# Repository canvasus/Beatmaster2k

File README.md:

# Beatmaster2k

A rudimentary step sequencer based on a Teensy 4.1 and a Novation Launchpad. 
It is mainly intended as a "jamming partner", not a full-fledged production tool.

Some basic features/specs:

- 7 Tracks. Can be set to output midi on serial, device or host ports
- 8 Patterns per track currently, but lots of room for expansion
- 64 Scenes, i.e combination of patterns

- Patterns are edited on the Launchpad. Works during playing
- Patterns can be set to any length between 1 and 128 steps
- Patterns have configurable speed

- Patterns and other settings stored on SD card

Component list:
- Teensy 4.1
- SD card
- ILI9341 display (touch is not used atm)
- 2 encoders
- 8 buttons via an MPC23017 expander
- Powered usb hub
- Novation Launchpad Mini Mk3

(prototype assembly)

(parts for 3D print and milling in Onshape)

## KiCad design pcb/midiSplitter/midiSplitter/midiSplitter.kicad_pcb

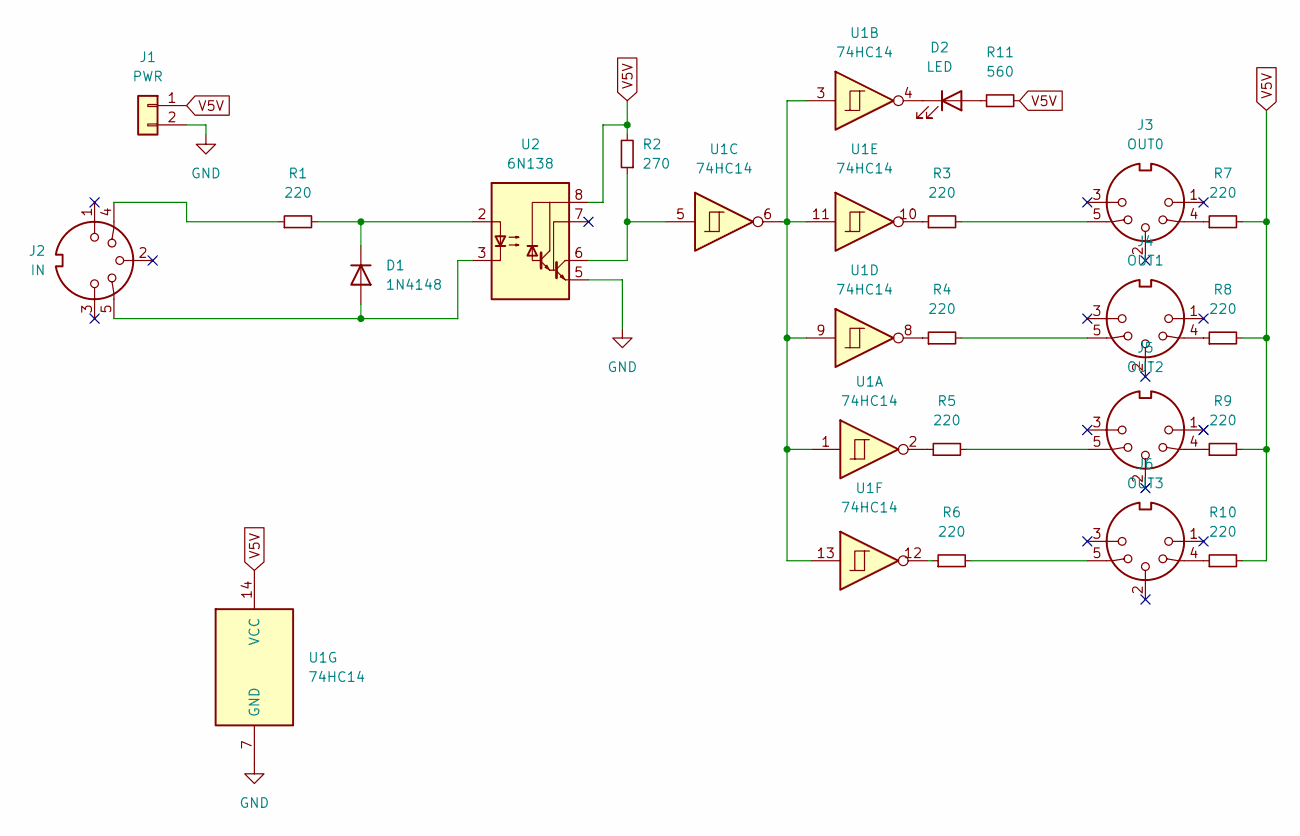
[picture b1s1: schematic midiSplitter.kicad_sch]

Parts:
D1: 1N4148; D_DO-35_SOD27_P7.62mm_Horizontal
D2: LED; LED_D3.0mm
J1: PWR; PinHeader_1x02_P2.54mm_Vertical
J2: IN; MIDI_DIN5
J3: OUT0; MIDI_DIN5
J4: OUT1; MIDI_DIN5
J5: OUT2; MIDI_DIN5
J6: OUT3; MIDI_DIN5
R1, R3, R4, R5, R6, R7, R8, R9, R10: 220; R_Axial_DIN0204_L3.6mm_D1.6mm_P5.08mm_Horizontal
R2: 270; R_Axial_DIN0204_L3.6mm_D1.6mm_P5.08mm_Horizontal
R11: 560; R_Axial_DIN0204_L3.6mm_D1.6mm_P5.08mm_Horizontal
U1: 74HC14; DIP-14_W7.62mm
U2: 6N138; DIP-8_W7.62mm

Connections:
GND: J1.2, U1.7 (GND), U2.5 (GND)
unnamed: D1.1 (K), R1.2, U2.2 (C1)
unnamed: D1.2 (A), J2.5, U2.3 (C2)
unnamed: D2.2 (A), R11.1
unnamed: J2.4, R1.1
unnamed: R2.1, U1.5, U2.6 (VO2)
unnamed: R3.1, U1.10
unnamed: J3.5, R3.2
unnamed: R4.1, U1.8
unnamed: J4.5, R4.2
unnamed: R5.1, U1.2
unnamed: J5.5, R5.2
unnamed: R6.1, U1.12
unnamed: J6.5, R6.2
unnamed: J3.4, R7.1
unnamed: J4.4, R8.1
unnamed: J5.4, R9.1
unnamed: J6.4, R10.1
unnamed: D2.1 (K), U1.4
unnamed: U1.1, U1.3, U1.6, U1.9, U1.11, U1.13
V5V: J1.1, R2.2, R7.2, R8.2, R9.2, R10.2, R11.2, U1.14 (VCC), U2.8 (VCC)

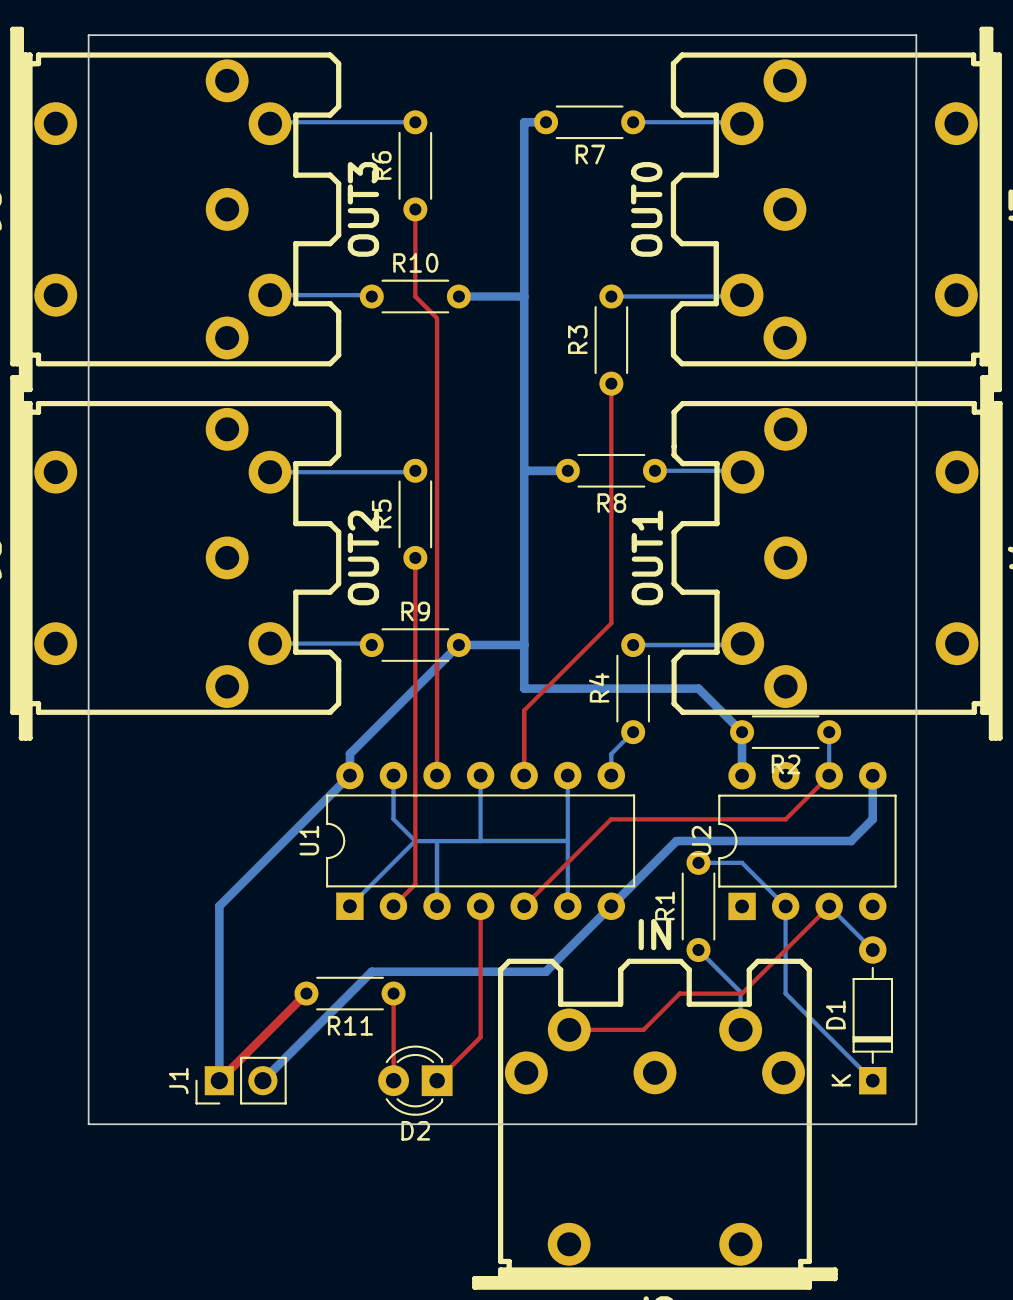
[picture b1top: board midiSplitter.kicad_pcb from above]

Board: 2 copper layers, 48.3 x 63.5 mm, 21 parts (0 on the bottom side), 21 nets.

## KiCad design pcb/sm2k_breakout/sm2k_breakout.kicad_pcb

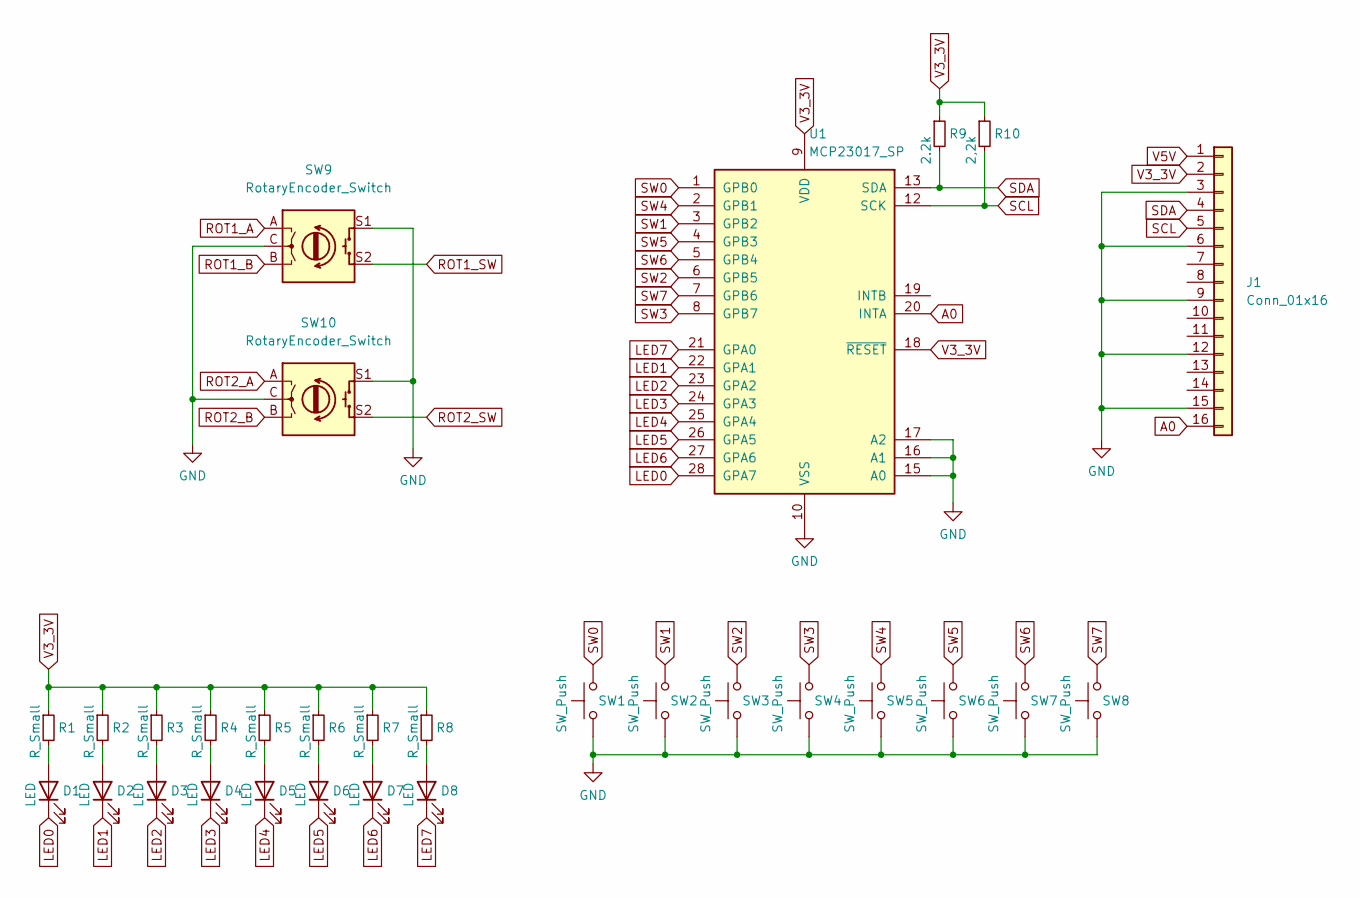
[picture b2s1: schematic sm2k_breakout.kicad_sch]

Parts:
D1, D2, D3, D4, D5, D6, D7, D8: LED; LED_D3.0mm
J1: Conn_01x16; IDC-Header_2x08_P2.54mm_Vertical
R1, R2, R3, R4, R5, R6, R7, R8: R_Small; R_0603_1608Metric_Pad0.98x0.95mm_HandSolder
R9: 2.2k; R_0603_1608Metric_Pad0.98x0.95mm_HandSolder
R10: 2,2k; R_0603_1608Metric_Pad0.98x0.95mm_HandSolder
SW1, SW2, SW3, SW4, SW5, SW6, SW7, SW8: SW_Push; SW_Cherry_MX_1.00u_PCB
SW9, SW10: RotaryEncoder_Switch; RotaryEncoder_Alps_EC11E-Switch_Vertical_H20mm_CircularMoun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
U1: MCP23017_SP; DIP-28_W7.62mm

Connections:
A0: J1.16, U1.20 (INTA)
GND: J1.3, J1.6, J1.9, J1.12, J1.15, SW1.1, SW2.1, SW3.1, SW4.1, SW5.1, SW6.1, SW7.1, SW8.1, SW9.C, SW9.S1, SW10.C, SW10.S1, U1.10 (VSS), U1.15 (A0), U1.16 (A1), U1.17 (A2)
LED0: D1.1 (K), U1.28 (GPA7)
LED1: D2.1 (K), U1.22 (GPA1)
LED2: D3.1 (K), U1.23 (GPA2)
LED3: D4.1 (K), U1.24 (GPA3)
LED4: D5.1 (K), U1.25 (GPA4)
LED5: D6.1 (K), U1.26 (GPA5)
LED6: D7.1 (K), U1.27 (GPA6)
LED7: D8.1 (K), U1.21 (GPA0)
unnamed: D1.2 (A), R1.2
unnamed: D2.2 (A), R2.2
unnamed: D3.2 (A), R3.2
unnamed: D4.2 (A), R4.2
unnamed: D5.2 (A), R5.2
unnamed: D6.2 (A), R6.2
unnamed: D7.2 (A), R7.2
unnamed: D8.2 (A), R8.2
ROT1_A: SW9.A
ROT1_B: SW9.B
ROT1_SW: SW9.S2
ROT2_A: SW10.A
ROT2_B: SW10.B
ROT2_SW: SW10.S2
SCL: J1.5, R10.2, U1.12 (SCK)
SDA: J1.4, R9.2, U1.13 (SDA)
SW0: SW1.2, U1.1 (GPB0)
SW1: SW2.2, U1.3 (GPB2)
SW2: SW3.2, U1.6 (GPB5)
SW3: SW4.2, U1.8 (GPB7)
SW4: SW5.2, U1.2 (GPB1)
SW5: SW6.2, U1.4 (GPB3)
SW6: SW7.2, U1.5 (GPB4)
SW7: SW8.2, U1.7 (GPB6)
V3_3V: J1.2, R1.1, R2.1, R3.1, R4.1, R5.1, R6.1, R7.1, R8.1, R9.1, R10.1, U1.9 (VDD), U1.18 (~RESET)
V5V: J1.1

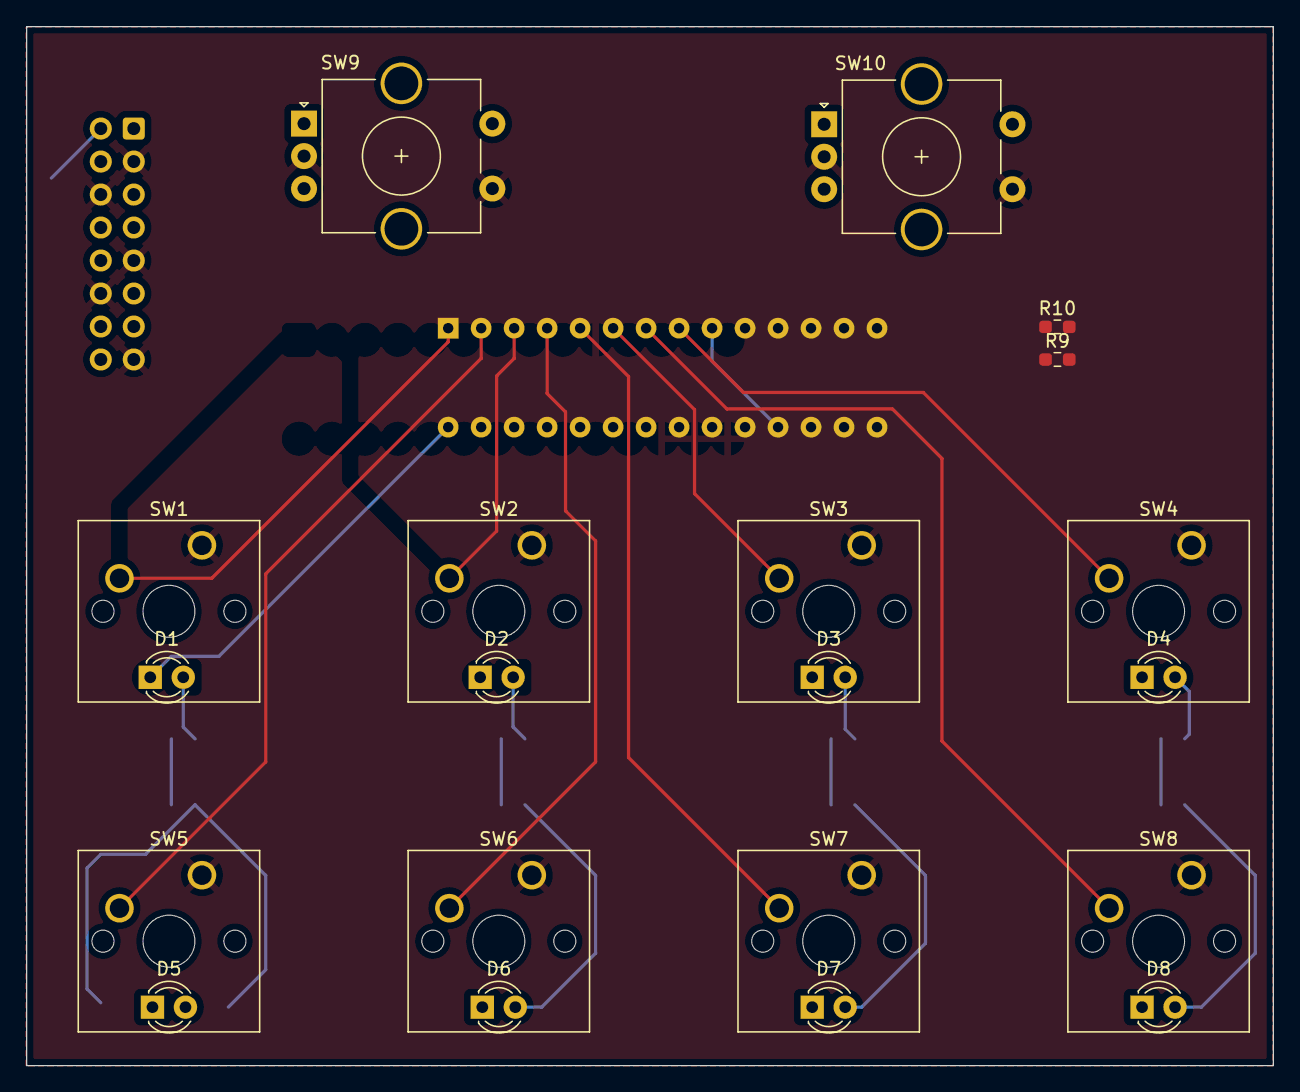
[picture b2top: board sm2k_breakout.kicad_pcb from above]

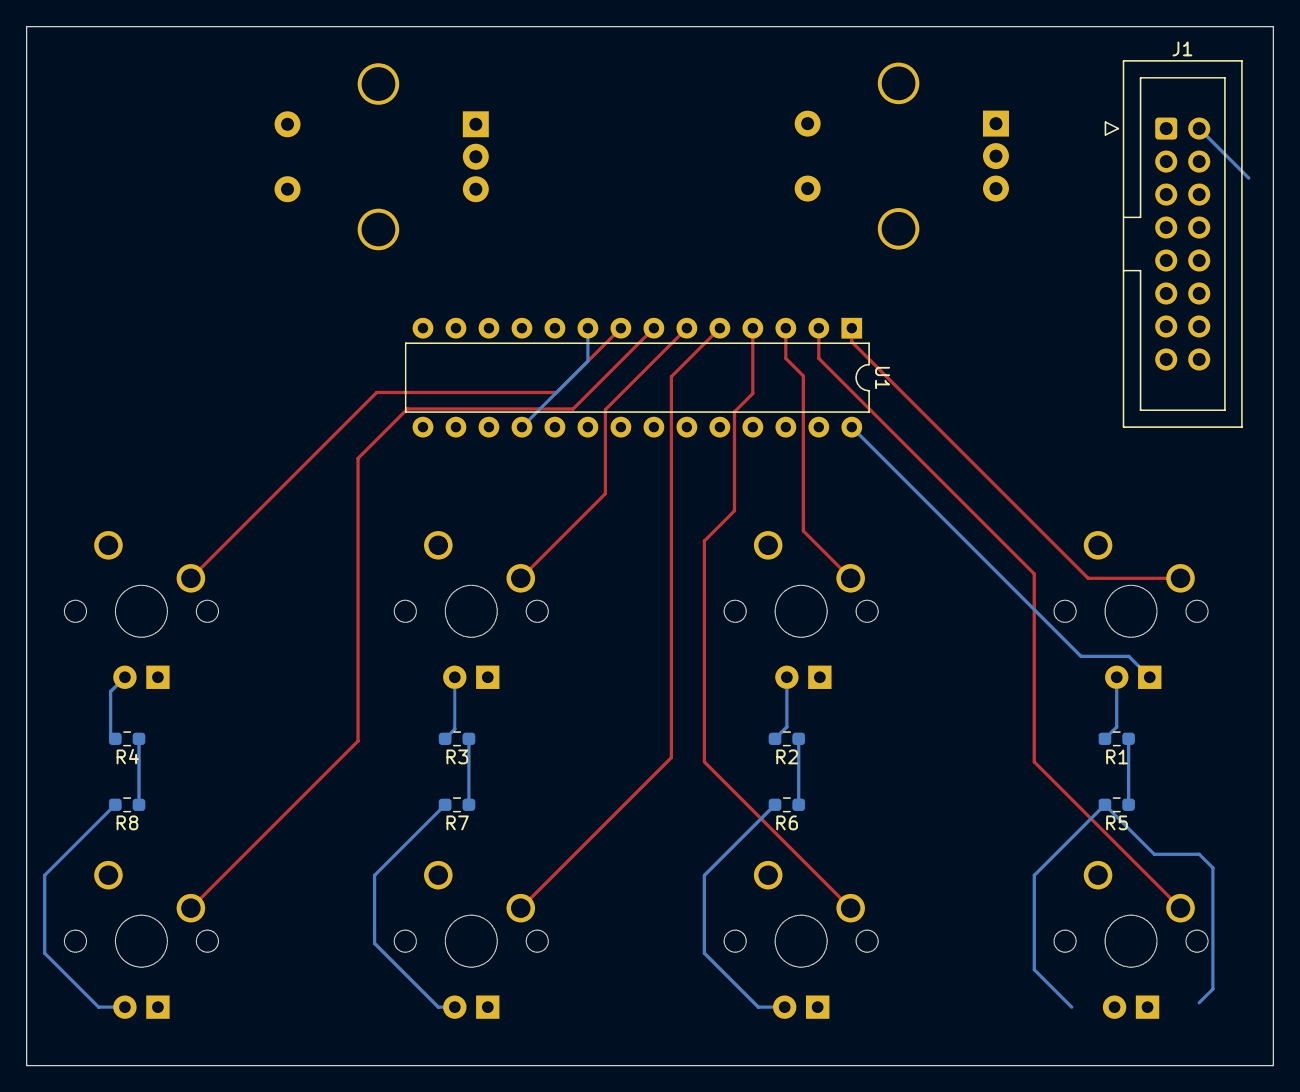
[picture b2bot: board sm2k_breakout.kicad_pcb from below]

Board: 2 copper layers, 96.0 x 80.0 mm, 30 parts (10 on the bottom side), 29 nets.

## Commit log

2022-09-29 Added sidechain
2022-10-02 cleanup
2022-10-09 SPI display
2022-10-15 new launchpad integration
2022-11-03 edit mode
2022-11-12 button matrix
2022-11-14 Ui fixes
2022-11-27 More UI
2022-12-11 Before new event storage
2022-12-11 removed audio, cued mute
2022-12-19 patterns and scenes + files
2022-12-26 Scenes and chain
2022-12-29 Tools and chaining
2022-12-30 UI bugfix
2023-01-02 fixed track change crash
2023-01-04 minor cleanup
2023-01-06 progress bar test and cleanup
2023-01-16 added internal voices for evaluation
2023-01-21 Added samples
